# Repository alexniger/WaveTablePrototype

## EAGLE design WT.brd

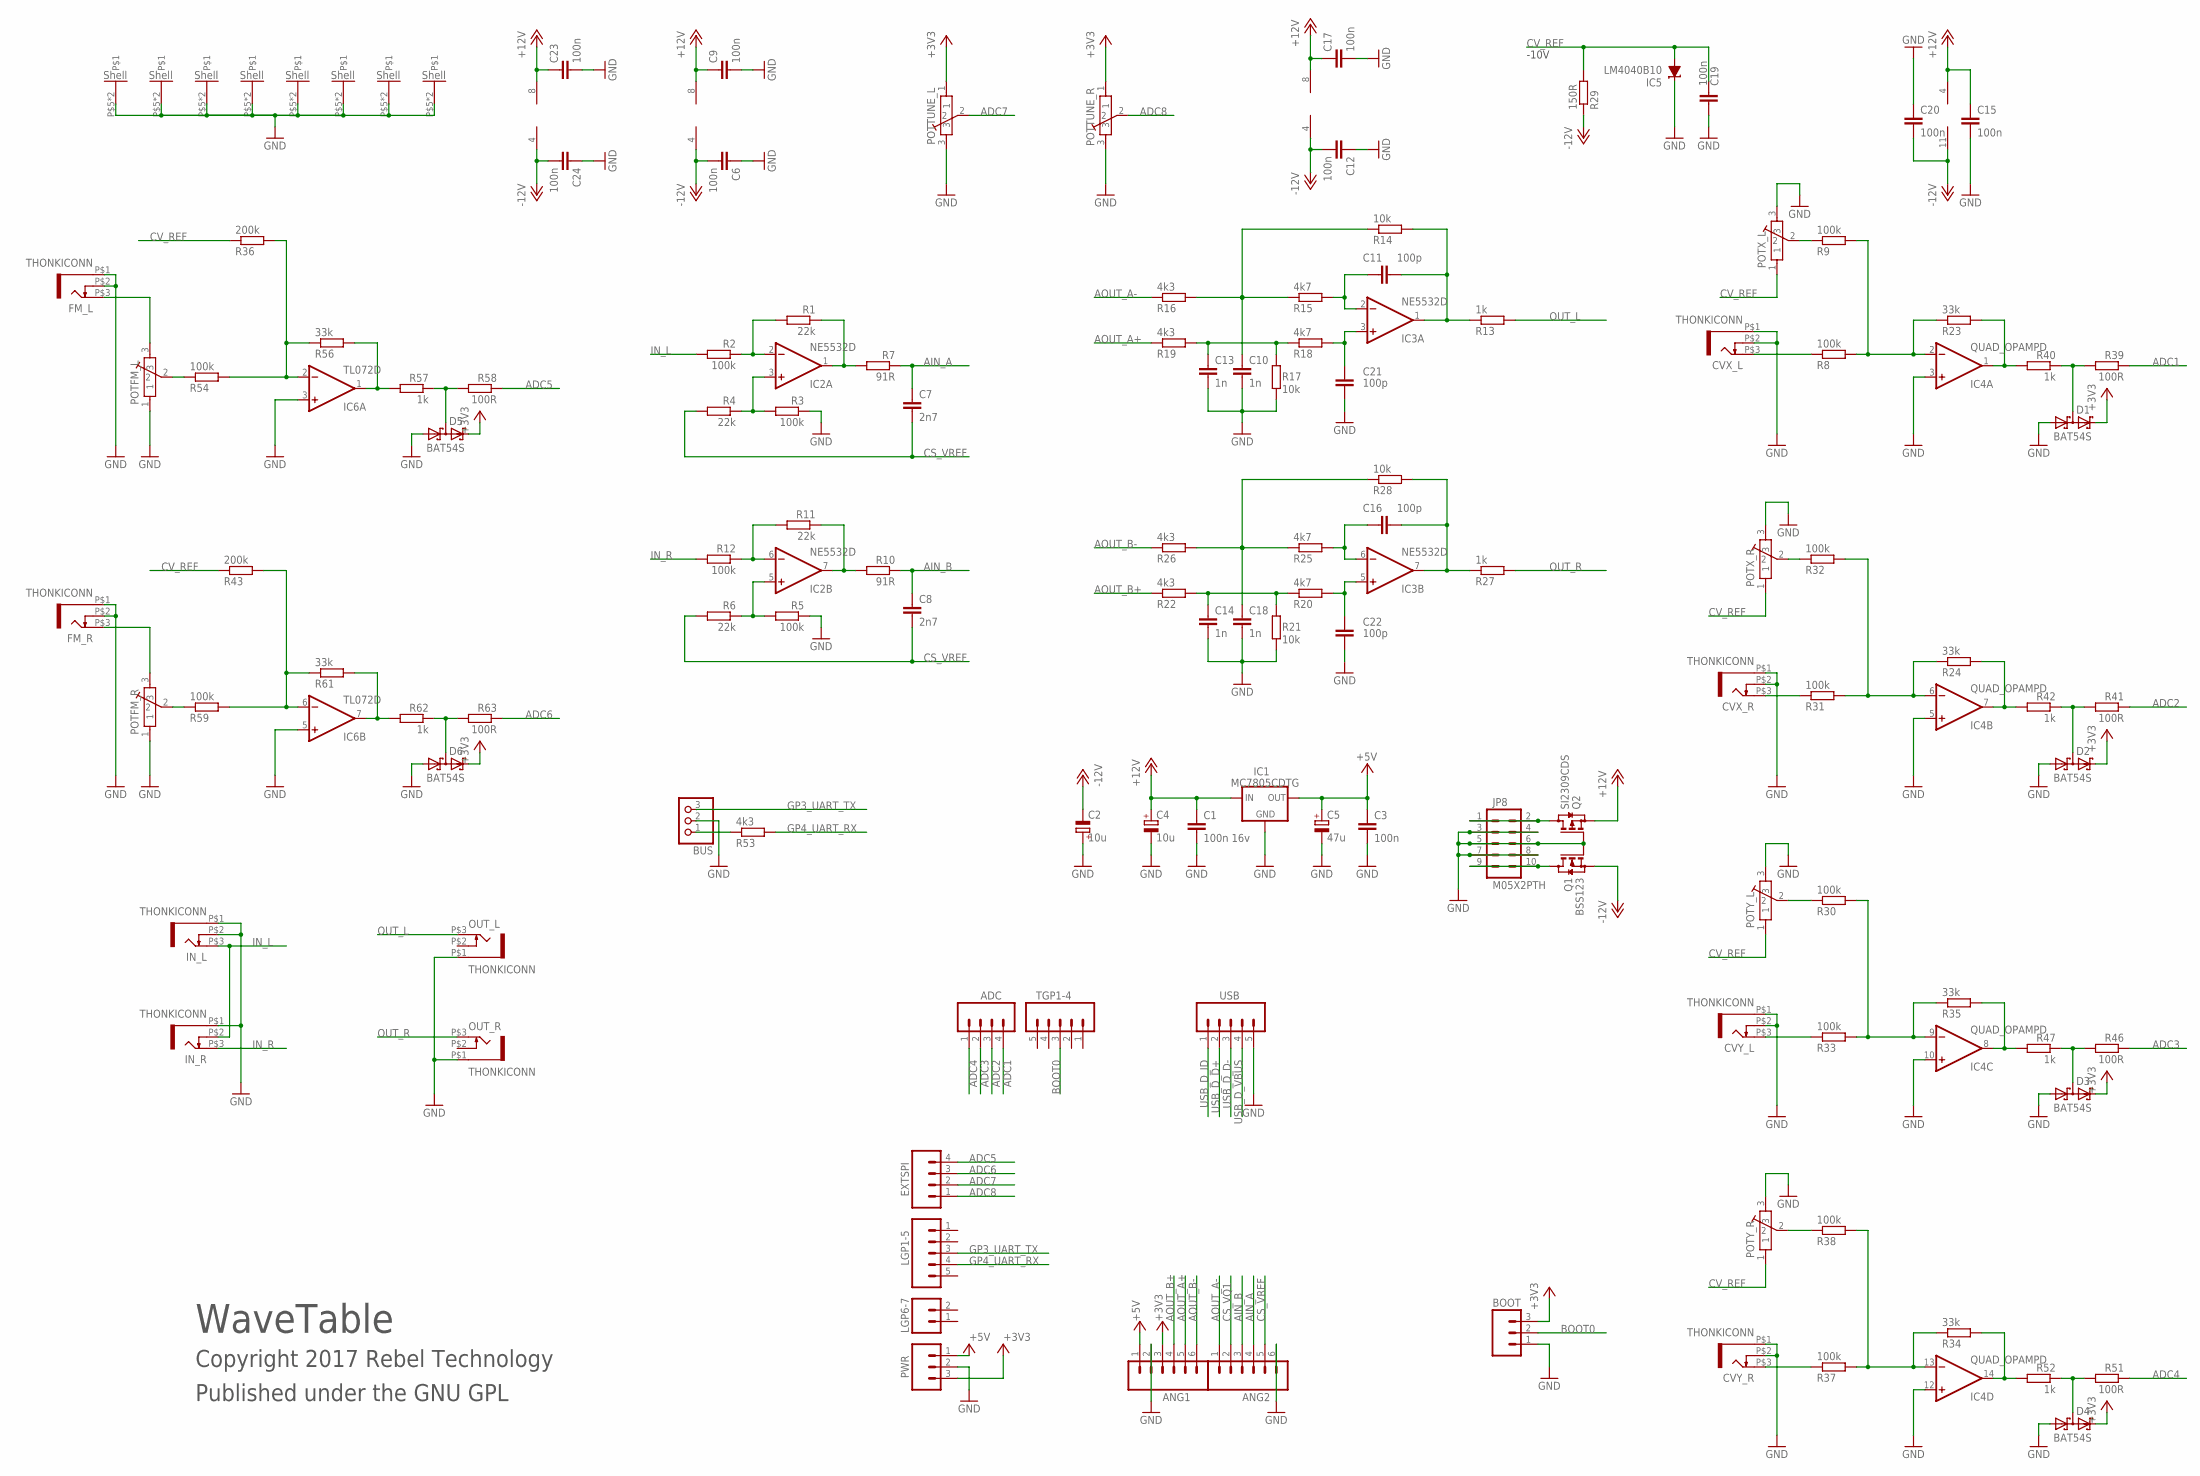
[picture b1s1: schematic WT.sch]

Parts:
ADC: M04PTH; 1X04
ANG1, ANG2: M06SIP; 1X06
BOOT: M03PTH; 1X03
BUS: CON-JST-1X03PH-TH; JST-B3B-PH-KL
C1: 100n 16v; C0603
C2, C4: 10u; CPOL-5
C3, C6, C9, C12, C15, C17, C19, C20, C23, C24: 100n; C0603
C5: 47u; PANASONIC_C
C7, C8: 2n7; C0603
C10, C13, C14, C18: 1n; C0603
C11, C16, C21, C22: 100p; C0603
CVX_L: THONKICONN
CVX_R: THONKICONN
CVY_L: THONKICONN
CVY_R: THONKICONN
D1, D2, D3, D4, D5, D6: BAT54S; SOT23
EXTSPI: M04PTH; 1X04
FM_L: THONKICONN
FM_R: THONKICONN
IC1: MC7805CDTG; DPACK
IC2, IC3: NE5532D; SO08
IC4: QUAD_OPAMPD; SO14
IC5: LM4040B10; DBZ_R-PDSO-G3
IC6: TL072D; SO08
IN_L: THONKICONN
IN_R: THONKICONN
JP8: M05X2PTH; AVR_ICSP
LGP1-5: M05PTH; 1X05
LGP6-7: M02PTH; 1X02
OUT_L: THONKICONN
OUT_R: THONKICONN
POTFM_L: POT-ALPS-RK09L1140
POTFM_R: POT-ALPS-RK09L1140
POTTUNE_L: POT-ALPS-RK09L1140
POTTUNE_R: POT-ALPS-RK09L1140
POTX_L: POT-ALPS-RK09L1140
POTX_R: POT-ALPS-RK09L1140
POTY_L: POT-ALPS-RK09L1140
POTY_R: POT-ALPS-RK09L1140
PWR: M03PTH; 1X03
Q1: BSS123; SOT23
Q2: SI2309CDS; SOT23
R1, R4, R6, R11: 22k; 0603
R2, R3, R5, R8, R9, R12, R30, R31, R32, R33, R37, R38, R54, R59: 100k; 0603
R7, R10: 91R; 0603
R13, R27, R40, R42, R47, R52, R57, R62: 1k; 0603
R14, R17, R21, R28: 10k; 0603
R15, R18, R20, R25: 4k7; 0603
R16, R19, R22, R26, R53: 4k3; 0603
R23, R24, R34, R35, R56, R61: 33k; 0603
R29: 150R; 0603
R36, R43: 200k; 0603
R39, R41, R46, R51, R58, R63: 100R; 0603
TGP1-4: M05PTH; 1X05
USB: M05PTH; 1X05

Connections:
+3V3: ANG1.3, BOOT.3, D1.2 (C2), D2.2 (C2), D3.2 (C2), D4.2 (C2), D5.2 (C2), D6.2 (C2), POTTUNE_L.1, POTTUNE_R.1, PWR.3
+5V: ANG1.1, C3.1, C5.+, IC1.3 (OUT), PWR.1
+12V: C1.1, C4.+, C9.1, C15.1, C17.1, C23.1, IC1.1 (IN), IC2.8 (V+), IC3.8 (V+), IC4.4 (V+), IC6.8 (V+), Q2.2 (S)
-12V: C2.-, C6.2, C12.2, C20.2, C24.2, IC2.4 (V-), IC3.4 (V-), IC4.11 (V-), IC6.4 (V-), Q1.2 (S), R29.1
ADC1: ADC.4, R39.1
ADC2: ADC.3, R41.1
ADC3: ADC.2, R46.1
ADC4: ADC.1, R51.1
ADC5: EXTSPI.4, R58.1
ADC6: EXTSPI.3, R63.1
ADC7: EXTSPI.2, POTTUNE_L.2
ADC8: EXTSPI.1, POTTUNE_R.2
AIN_A: ANG2.4, C7.1, R7.1
AIN_B: ANG2.3, C8.1, R10.1
AOUT_A+: ANG1.5, R19.1
AOUT_A-: ANG2.1, R16.1
AOUT_B+: ANG1.4, R22.1
AOUT_B-: ANG1.6, R26.1
BOOT0: BOOT.2, TGP1-4.3
CS_VQ1: ANG2.2
CS_VREF: ANG2.5, C7.2, C8.2, R4.2, R6.2
CV_REF: C19.1, IC5.2 (A), POTX_L.1, POTX_R.1, POTY_L.1, POTY_R.1, R29.2, R36.1, R43.1
EXT_UART_RX: BUS.1, R53.1
GND: ANG1.2, ANG2.6, BOOT.1, BUS.2, C1.2, C2.+, C3.2, C4.-, C5.-, C6.1, C9.2, C10.2, C12.1, C13.2, C14.2, C15.2, C17.2, C18.2, C19.2, C20.1, C21.2, C22.2, C23.2, C24.1, CVX_L.P$1 (5), CVX_L.P$2 (4), CVX_R.P$1 (5), CVX_R.P$2 (4), CVY_L.P$1 (5), CVY_L.P$2 (4), CVY_R.P$1 (5), CVY_R.P$2 (4), D1.1 (A1), D2.1 (A1), D3.1 (A1), D4.1 (A1), D5.1 (A1), D6.1 (A1), FM_L.P$1 (5), FM_L.P$2 (4), FM_R.P$1 (5), FM_R.P$2 (4), IC1.4 (GND), IC4.3 (+IN), IC4.5 (+IN), IC4.10 (+IN), IC4.12 (+IN), IC5.1 (C), IC6.3 (+IN), IC6.5 (+IN), IN_L.P$1 (5), IN_L.P$2 (4), IN_R.P$1 (5), JP8.3, JP8.4, JP8.5, JP8.6, JP8.7, JP8.8, OUT_L.P$1 (5), OUT_R.P$1 (5), POTFM_L.1, POTFM_L.P$5, POTFM_L.P$6, POTFM_R.1, POTFM_R.P$5, POTFM_R.P$6, POTTUNE_L.3, POTTUNE_L.P$5, POTTUNE_L.P$6, POTTUNE_R.3, POTTUNE_R.P$5, POTTUNE_R.P$6, POTX_L.3, POTX_L.P$5, POTX_L.P$6, POTX_R.3, POTX_R.P$5, POTX_R.P$6, POTY_L.3, POTY_L.P$5, POTY_L.P$6, POTY_R.3, POTY_R.P$5, POTY_R.P$6, PWR.2, Q1.1 (G), Q2.1 (G), R3.1, R5.1, R17.1, R21.1, USB.5
GP3_UART_TX: BUS.3, LGP1-5.3
GP4_UART_RX: LGP1-5.4, R53.2
IN_L: IN_L.P$3 (3), IN_R.P$2 (4), R2.2
IN_R: IN_R.P$3 (3), R12.2
unnamed: IC2.1 (OUT), R1.1, R7.2
unnamed: IC2.3 (+IN), R3.2, R4.1
unnamed: CVX_L.P$3 (3), R8.1
unnamed: IC2.5 (+IN), R5.2, R6.1
unnamed: IC2.6 (-IN), R11.2, R12.1
unnamed: IC4.9 (-IN), R30.2, R33.2, R35.1
unnamed: C11.1, IC3.2 (-IN), R15.2
unnamed: JP8.9, JP8.10, Q1.3 (D)
unnamed: IC2.2 (-IN), R1.2, R2.1
unnamed: IC2.7 (OUT), R10.2, R11.1
unnamed: C21.1, IC3.3 (+IN), R18.2
unnamed: JP8.1, JP8.2, Q2.3 (D)
unnamed: IC4.2 (-IN), R8.2, R9.2, R23.1
unnamed: POTX_L.2, R9.1
unnamed: C13.1, R17.2, R18.1, R19.2
unnamed: D1.3 (C1A2), R39.2, R40.1
unnamed: IC4.1 (OUT), R23.2, R40.2
unnamed: C16.2, IC3.7 (OUT), R27.1, R28.2
unnamed: CVX_R.P$3 (3), R31.1
unnamed: IC4.6 (-IN), R24.1, R31.2, R32.2
unnamed: POTX_R.2, R32.1
unnamed: IC4.7 (OUT), R24.2, R42.2
unnamed: D2.3 (C1A2), R41.2, R42.1
unnamed: C18.1, R25.1, R26.2, R28.1
unnamed: CVY_L.P$3 (3), R33.1
unnamed: C16.1, IC3.6 (-IN), R25.2
unnamed: POTY_L.2, R30.1
unnamed: IC4.8 (OUT), R35.2, R47.2
unnamed: D3.3 (C1A2), R46.2, R47.1
unnamed: C22.1, IC3.5 (+IN), R20.2
unnamed: CVY_R.P$3 (3), R37.1
unnamed: C14.1, R20.1, R21.2, R22.2
unnamed: IC4.13 (-IN), R34.1, R37.2, R38.2
unnamed: POTY_R.2, R38.1
unnamed: IC4.14 (OUT), R34.2, R52.2
unnamed: D4.3 (C1A2), R51.2, R52.1
unnamed: C11.2, IC3.1 (OUT), R13.1, R14.2
unnamed: C10.1, R14.1, R15.1, R16.2
unnamed: POTFM_L.2, R54.1
unnamed: IC6.1 (OUT), R56.2, R57.2
unnamed: D5.3 (C1A2), R57.1, R58.2
unnamed: POTFM_R.2, R59.1
unnamed: IC6.6 (-IN), R43.2, R59.2, R61.1
unnamed: FM_R.P$3 (3), POTFM_R.3
unnamed: IC6.7 (OUT), R61.2, R62.2
unnamed: D6.3 (C1A2), R62.1, R63.2
unnamed: IC6.2 (-IN), R36.2, R54.2, R56.1
unnamed: FM_L.P$3 (3), POTFM_L.3
OUT_L: OUT_L.P$3 (3), R13.2
OUT_R: OUT_R.P$3 (3), R27.2
USB_D_D+: USB.2
USB_D_D-: USB.3
USB_D_ID: USB.1
USB_D_VBUS: USB.4

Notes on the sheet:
WaveTable
Copyright 2017 Rebel Technology
Published under the GNU GPL
-10V

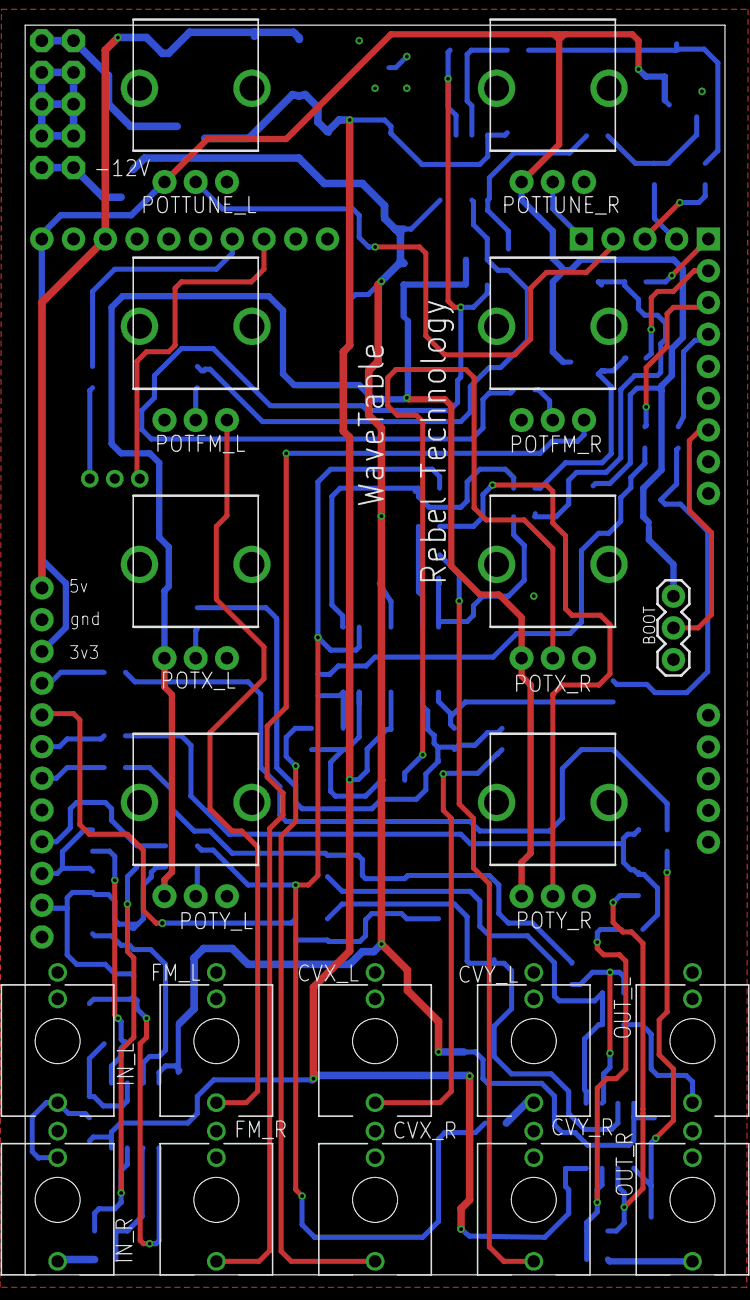
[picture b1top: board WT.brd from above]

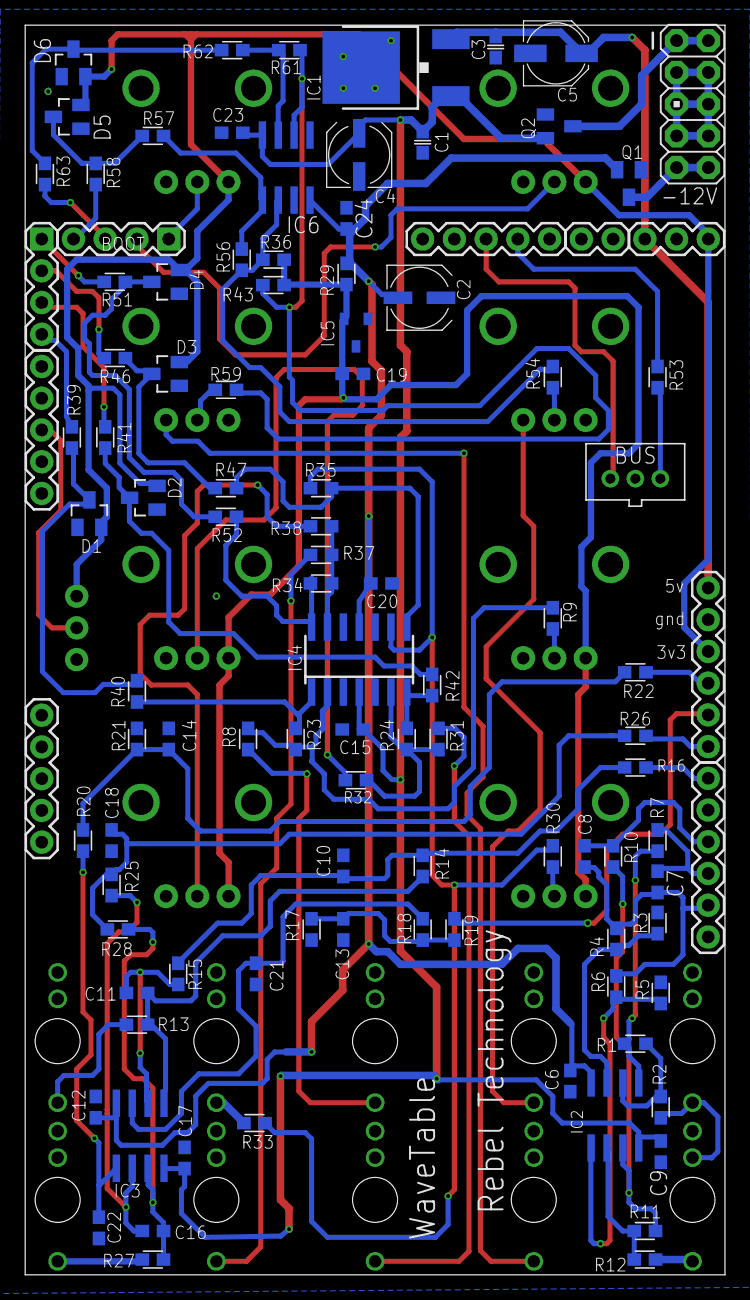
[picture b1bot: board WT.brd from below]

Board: 2 copper layers, 56.0 x 100.0 mm, 124 parts (105 on the bottom side), 77 nets.

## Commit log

2018-07-31 WT shematic + board upload
2018-07-31 update board
2018-08-06 finished routing
2018-08-06 12 mil clearance update
2018-08-06 update name
2018-08-07 update final board
2018-08-07 last update
2019-12-17 add patch via upload
    The patch is DualMorphing2DTestPatch.hpp.
    requires MorphOsc, OscSelector, WTFactory and the sample source : alien10752.h
2019-12-17 FM introduced
2019-12-18 update prototype

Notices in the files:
parts and their libraries:
SparkFun: Licensing: CC v3.0 Share-Alike You are welcome to use this library for commercial purposes.
